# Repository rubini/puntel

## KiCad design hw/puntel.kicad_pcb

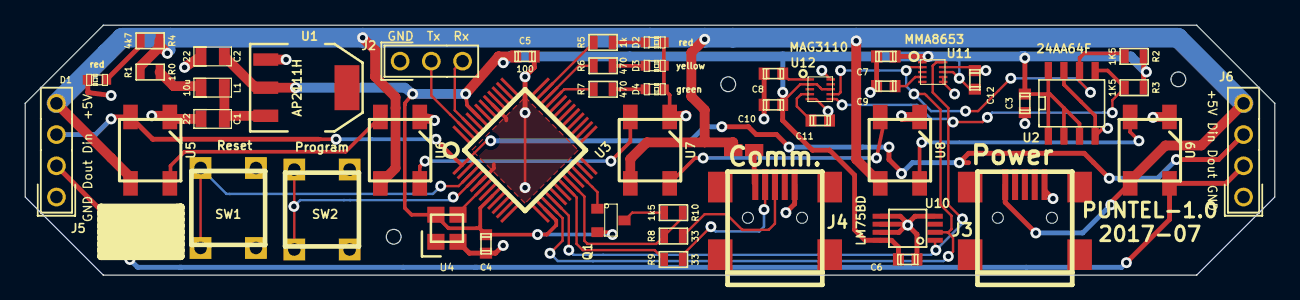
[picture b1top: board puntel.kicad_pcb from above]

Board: 2 copper layers, 101.6 x 20.3 mm, 48 parts (0 on the bottom side), 35 nets.

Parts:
C1, C2: 22; SM0805-rubi
C3, C6, C7, C8, C9, C10, C11, C12: 100n; C_0603-rubi
C4, C5: 100; C_0603-rubi
D1, D2: red; LED-0603-rubi
D3: yellow; LED-0603-rubi
D4: green; LED-0603-rubi
J2: STRIP-3; strip-3
J3: USB-power; USB_MINI_B-SMD
J4: USB-prog; USB_MINI_B-SMD
J5, J6: STRIP-4; strip-4
JS1: SOLDER-JUMPER; solder-jumper
L1: 10u; SM0805-rubi
Q1: DTA114; SOT23-rubi
R1: 1R0; R0603-rubi
R2, R3: 1K5; R0603-rubi
R4: 4k7; R0603-rubi
R5: 1k; R0603-rubi
R6, R7: 470; R0603-rubi
R8, R9: 33; R0603-rubi
R10: 1k5; R0603-rubi
SW1, SW2: BUTTON
U1: AP2111H; LDO-SOT223
U2: 24AA64F; SO8E
U3: LPC11U23FBD48; lqfp-48-rubi
U4: CLOCK-MODULE; Si501
U5, U6, U7, U8, U9: WS2812B
U10: LM75BD; SSOP8
U11: MMA8653; dfn-10
U12: MAG3110; dfn-10

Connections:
+3.3V: C2.1, C3.1, C4.1, C5.1, C6.1, C7.1, C10.1, C12.1, Q1.2, R2.1, R3.1, U1.2, U2.1, U2.2, U2.3, U2.8, U3.8, U3.14, U3.44, U4.4, U10.8, U11.1, U11.8, U12.2, U12.8
+5V: J3.1, J5.4, J6.4, JS1.1, R1.1, R4.1, U5.1, U6.1, U7.1, U8.1, U9.1
/DM: J4.2, R9.2
/DP: J4.3, R8.2
/Din: J5.3, J6.3, U3.1, U5.4
/Dout: J5.2, J6.2, U9.2
/GLED: R7.1, U3.33
/PRG*: SW2.1, SW2.2, U3.4
/RLED: R5.1, U3.35
/RST*: SW1.1, SW1.2, U3.3
/RXD: J2.3, U3.46
/SCL: R2.2, U2.6, U3.15, U10.2, U11.2, U12.7
/SDA: R3.2, U2.5, U3.16, U10.1, U11.10, U12.6
/TXD: J2.2, U3.47
/USBC*: Q1.1, U3.22
/YLED: R6.1, U3.34
GND: C1.2, C2.2, C3.2, C4.2, C5.2, C6.2, C7.2, C8.2, C9.2, C10.2, C11.2, C12.2, D1.2, D2.2, D3.2, D4.2, J2.1, J3.5, J4.5, J5.1, J6.1, SW1.3, SW1.4, SW2.3, SW2.4, U1.1, U2.4, U2.7, U3.5, U3.41, U4.2, U5.3, U6.3, U7.3, U8.3, U9.3, U10.4, U10.5, U10.6, U10.7, U11.6, U11.7, U11.9, U12.5, U12.10
unnamed: D1.1, R4.2
unnamed: C8.1, U12.1
unnamed: C11.1, U12.4
unnamed: C9.1, U11.4
unnamed: U8.2, U9.4
unnamed: U7.2, U8.4
unnamed: D4.1, R7.2
unnamed: J4.1, JS1.2
unnamed: R8.1, R10.1, U3.20
unnamed: U6.2, U7.4
unnamed: U5.2, U6.4
unnamed: U3.6, U4.3
unnamed: R9.1, U3.19
unnamed: Q1.3, R10.2
unnamed: C1.1, L1.1, U1.3
unnamed: D2.1, R5.2
unnamed: D3.1, R6.2
unnamed: L1.2, R1.2

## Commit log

2017-07-17 hw/lib: added my library files
2017-07-17 hw: first version unrouted (with uext)
2017-07-17 hw: routed (without uext)
2017-07-18 hw: minor changes
2017-07-18 hw: beautify schematic file (no change)
2017-07-18 hw: clean-up pcb
2017-07-18 hw/output: the files sent for printing
2017-08-20 sw: my usual base stuff, in simplified form
2017-08-21 sw/tests: added trivial blink test
2017-08-21 sw/tests: added two trivial tests
2017-08-23 sw/board.h: added led definitions
2017-08-23 lib/gpio-11xx: fix pullup-pulldown setup
2017-08-23 sw: the main program
2017-08-23 sw: use orange, not green, and a little stronger
2017-08-30 hw: added puntel.pdf (output from kicad)
